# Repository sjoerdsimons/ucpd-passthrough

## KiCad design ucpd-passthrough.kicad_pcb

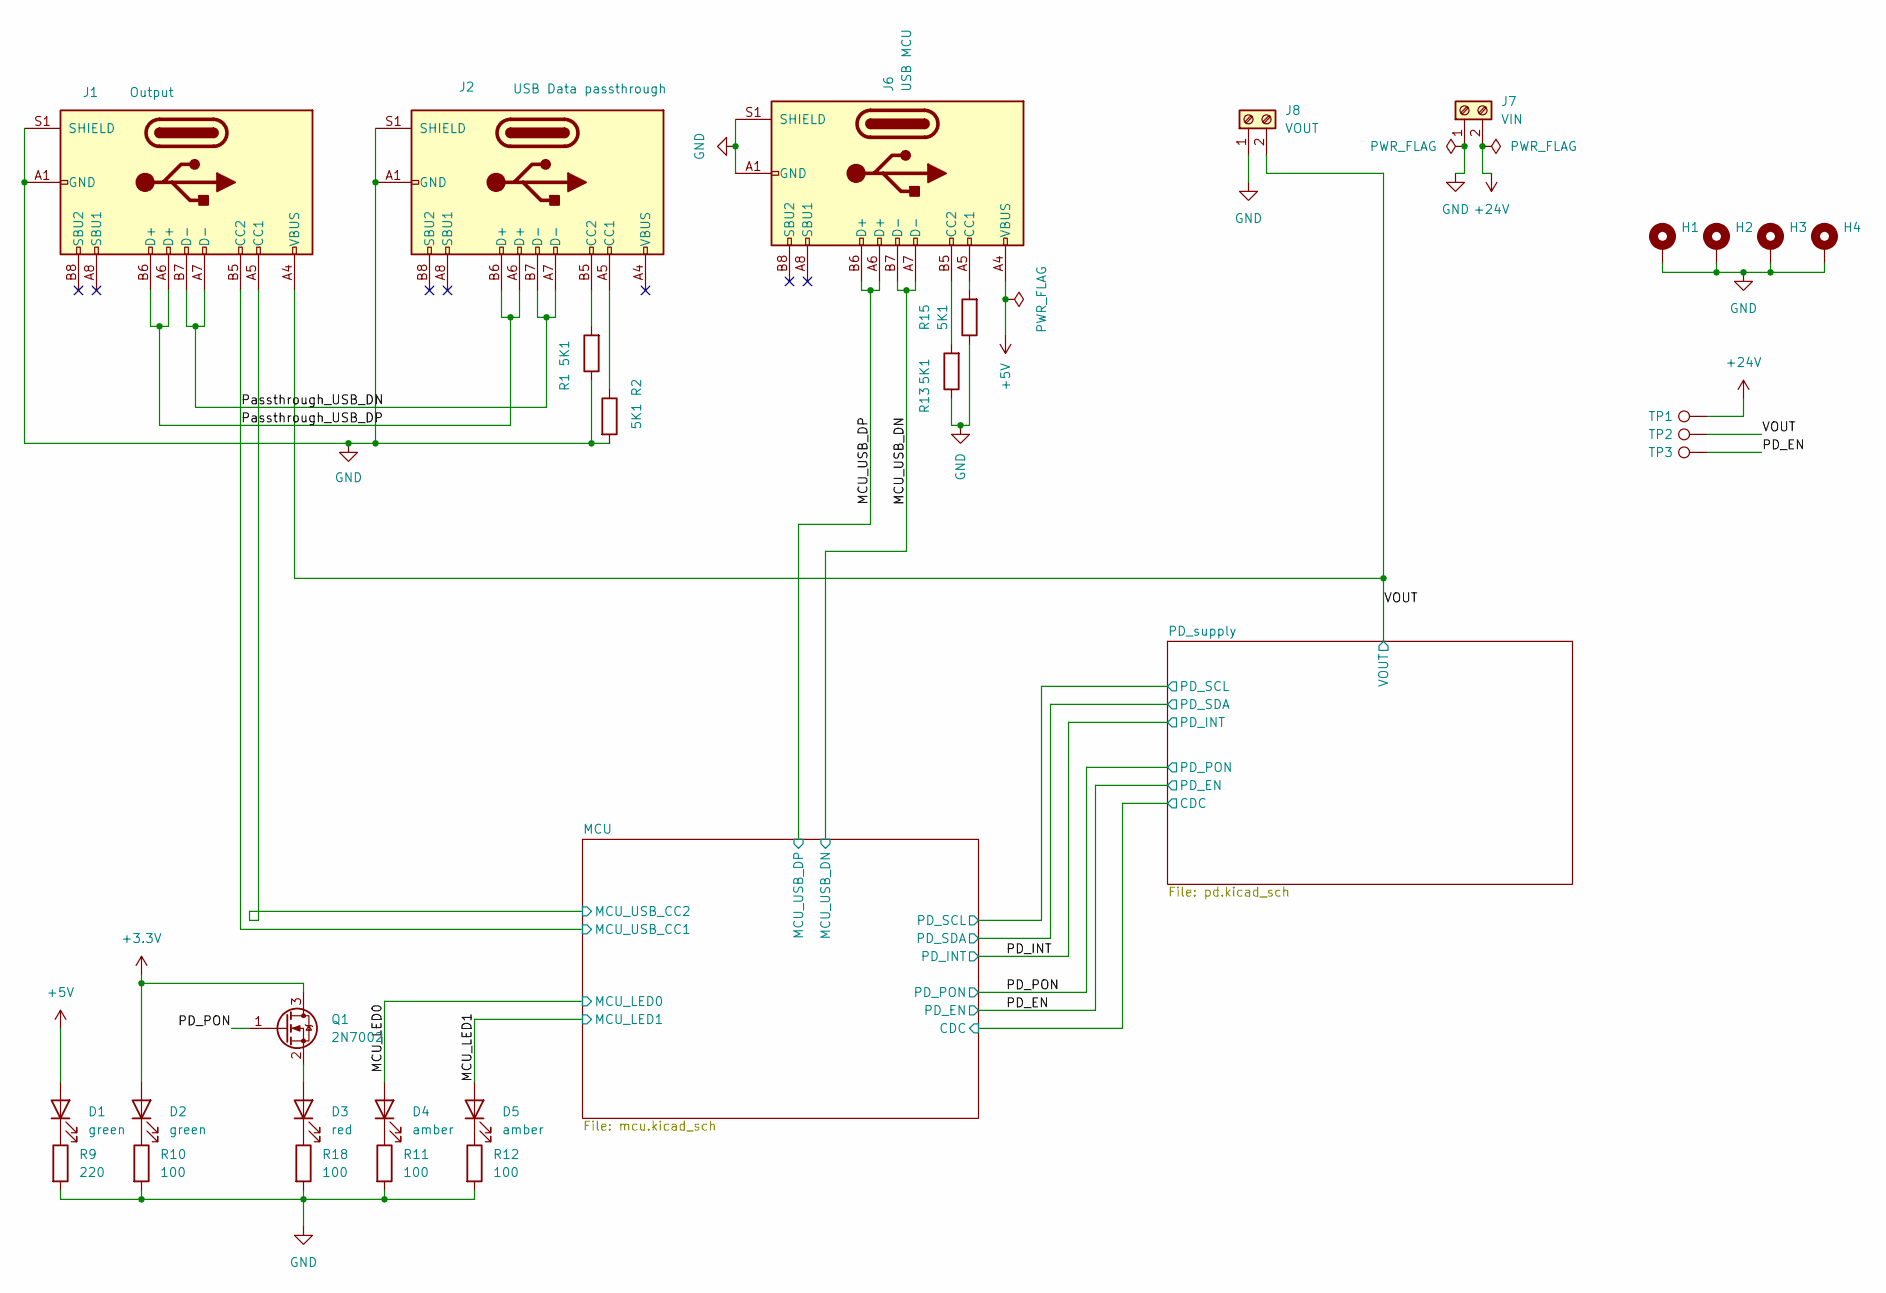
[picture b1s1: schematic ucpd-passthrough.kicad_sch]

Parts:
D1, D2: green; LED_0603_1608Metric; DigiKey 732-4980-1-ND
D3: red; LED_0603_1608Metric; DigiKey 732-4978-1-ND
D4, D5: amber; LED_0603_1608Metric; DigiKey 732-150060AS75000CT-ND
H1, H2, H3, H4: MountingHole_Pad; MountingHole_2.2mm_M2_DIN965_Pad
J1: Output; USB_C_Receptacle_GCT_USB4105-xx-A_16P_TopMnt_Horizontal; DigiKey 2073-USB4105-GF-ACT-ND
J2: USB Data passthrough; USB_C_Receptacle_GCT_USB4105-xx-A_16P_TopMnt_Horizontal; DigiKey 2073-USB4105-GF-ACT-ND
J6: USB MCU; USB_C_Receptacle_GCT_USB4105-xx-A_16P_TopMnt_Horizontal; DigiKey 2073-USB4105-GF-ACT-ND
J7: VIN; TerminalBlock_MaiXu_MX126-5.0-02P_1x02_P5.00mm; DigiKey 732-10955-ND
J8: VOUT; TerminalBlock_MaiXu_MX126-5.0-02P_1x02_P5.00mm; DigiKey 732-10955-ND
Q1: 2N7002; SOT-23; DigiKey 5399-2N7002CT-ND
R1, R2, R13, R15: 5K1; R_0603_1608Metric; DigiKey 13-RC0603FR-105K1LCT-ND
R9: 220; R_0603_1608Metric; DigiKey 311-220HRCT-ND
R10, R11, R12, R18: 100; R_0603_1608Metric; DigiKey 311-100HRCT-ND
TP1, TP2: TestPoint; TestPoint_Pad_D2.0mm
TP3: TestPoint; TestPoint_Pad_D1.0mm

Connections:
+3.3V: D2.2 (A), Q1.3 (D); also elsewhere on the board
+5V: D1.2 (A), J6.A4 (VBUS), J6.A9 (VBUS), J6.B4 (VBUS), J6.B9 (VBUS); also elsewhere on the board
+24V: J7.2, TP1.1; also elsewhere on the board
/MCU/MCU_USB_CC2: J1.A5 (CC1); also elsewhere on the board
/MCU_LED0: D4.2 (A); also elsewhere on the board
/MCU_LED1: D5.2 (A); also elsewhere on the board
/MCU_USB_DN: J6.A7 (D-), J6.B7 (D-); also elsewhere on the board
/MCU_USB_DP: J6.A6 (D+), J6.B6 (D+); also elsewhere on the board
/PD_EN: TP3.1; also elsewhere on the board
/PD_PON: Q1.1 (G); also elsewhere on the board
/VOUT: J1.A4 (VBUS), J1.A9 (VBUS), J1.B4 (VBUS), J1.B9 (VBUS), J8.2, TP2.1; also elsewhere on the board
GND: H1.1, H2.1, H3.1, H4.1, J1.A1 (GND), J1.A12 (GND), J1.B1 (GND), J1.B12 (GND), J1.S1 (SHIELD), J2.A1 (GND), J2.A12 (GND), J2.B1 (GND), J2.B12 (GND), J2.S1 (SHIELD), J6.A1 (GND), J6.A12 (GND), J6.B1 (GND), J6.B12 (GND), J6.S1 (SHIELD), J7.1, J8.1, R1.1, R2.2, R9.2, R10.2, R11.2, R12.2, R13.1, R15.1, R18.2; also elsewhere on the board
unnamed: D1.1 (K), R9.1
unnamed: D2.1 (K), R10.1
unnamed: D3.2 (A), Q1.2 (S)
unnamed: D3.1 (K), R18.1
unnamed: D4.1 (K), R11.1
unnamed: D5.1 (K), R12.1
unnamed: J2.A5 (CC1), R2.1
unnamed: J2.B5 (CC2), R1.2
unnamed: J6.A5 (CC1), R15.2
unnamed: J6.B5 (CC2), R13.2

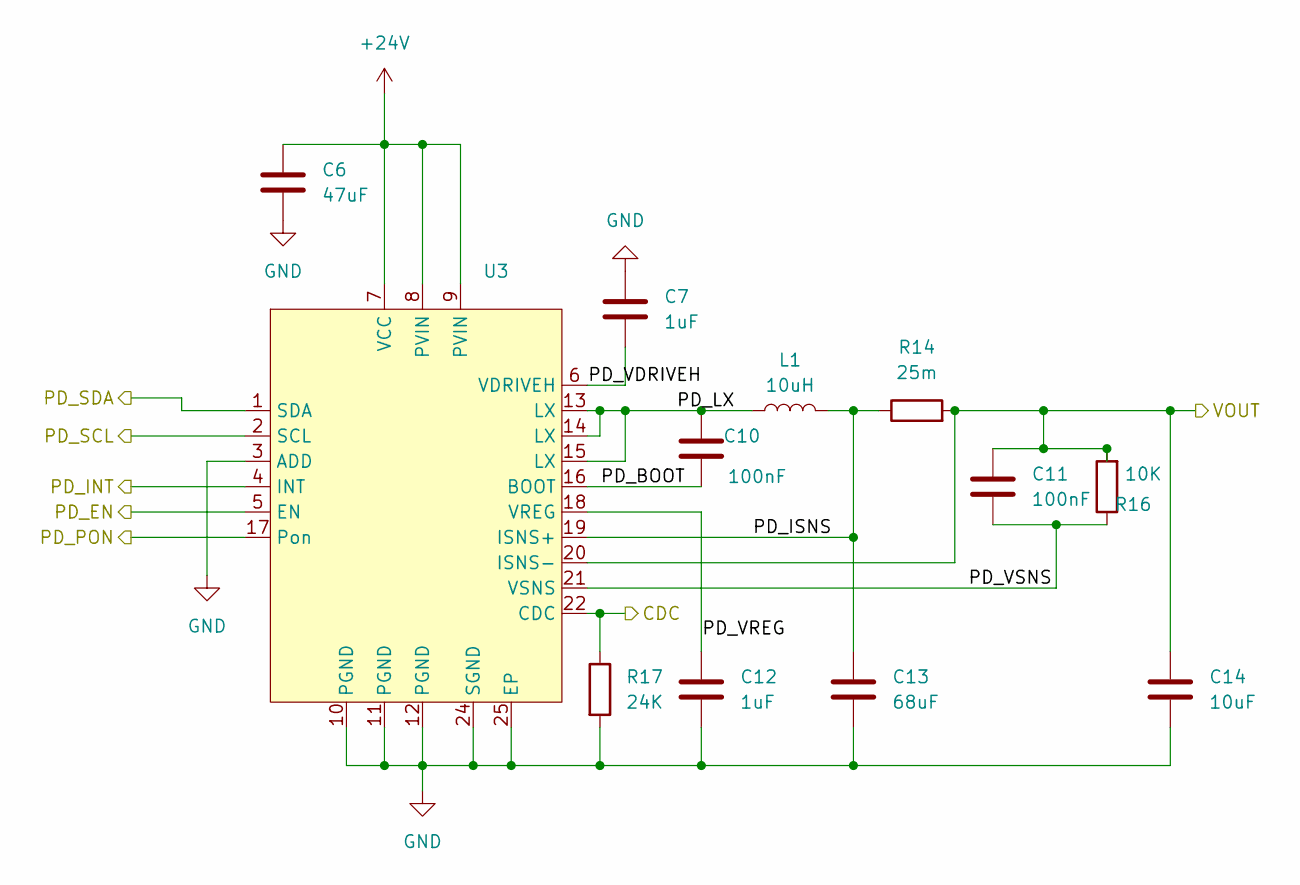
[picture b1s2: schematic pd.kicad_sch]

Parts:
C6: 47uF; CAPC6153X670N; DigiKey 490-16295-1-ND
C7, C12: 1uF; C_0603_1608Metric; DigiKey 1276-1861-1-ND
C10, C11: 100nF; C_0603_1608Metric; DigiKey 1276-1935-1-ND
C13: 68uF; CAP_KRM55_MUR; DigiKey 490-16293-1-ND
C14: 10uF; C_0603_1608Metric; DigiKey 490-GRM188R6YA106MA73JCT-ND
L1: 10uH; IND_SPRH1210-100M; DigiKey 4044-SPRH1210-100MCT-ND
R14: 25m; R_2512_6332Metric_Pad1.40x3.35mm_HandSolder; DigiKey YAG2169CT-ND
R16: 10K; R_0603_1608Metric; DigiKey 311-10.0KHRCT-ND
R17: 24K; R_0603_1608Metric; DigiKey 311-24.0KHRCT-ND
U3: QFN_D01PUR_STM; DigiKey 497-STPD01PURCT-ND

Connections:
+24V: C6.1, U3.7 (VCC), U3.8 (PVIN), U3.9 (PVIN); also elsewhere on the board
/MCU/CDC: R17.1, U3.22 (CDC); also elsewhere on the board
/MCU/PD_SCL: U3.2 (SCL); also elsewhere on the board
/MCU/PD_SDA: U3.1 (SDA); also elsewhere on the board
/PD_EN: U3.5 (EN); also elsewhere on the board
/PD_INT: U3.4 (INT); also elsewhere on the board
/PD_PON: U3.17 (Pon); also elsewhere on the board
/PD_supply/PD_BOOT: C10.1, U3.16 (BOOT)
/PD_supply/PD_ISNS: C13.1, L1.2, R14.1, U3.19 (ISNS+)
/PD_supply/PD_LX: C10.2, L1.1, U3.13 (LX), U3.14 (LX), U3.15 (LX)
/PD_supply/PD_VDRIVEH: C7.2, U3.6 (VDRIVEH)
/PD_supply/PD_VREG: C12.1, U3.18 (VREG)
/PD_supply/PD_VSNS: C11.1, R16.1, U3.21 (VSNS)
/VOUT: C11.2, C14.1, R14.2, R16.2, U3.20 (ISNS-); also elsewhere on the board
GND: C6.2, C7.1, C12.2, C13.2, C14.2, R17.2, U3.3 (ADD), U3.10 (PGND), U3.11 (PGND), U3.12 (PGND), U3.24 (SGND), U3.25 (EP); also elsewhere on the board

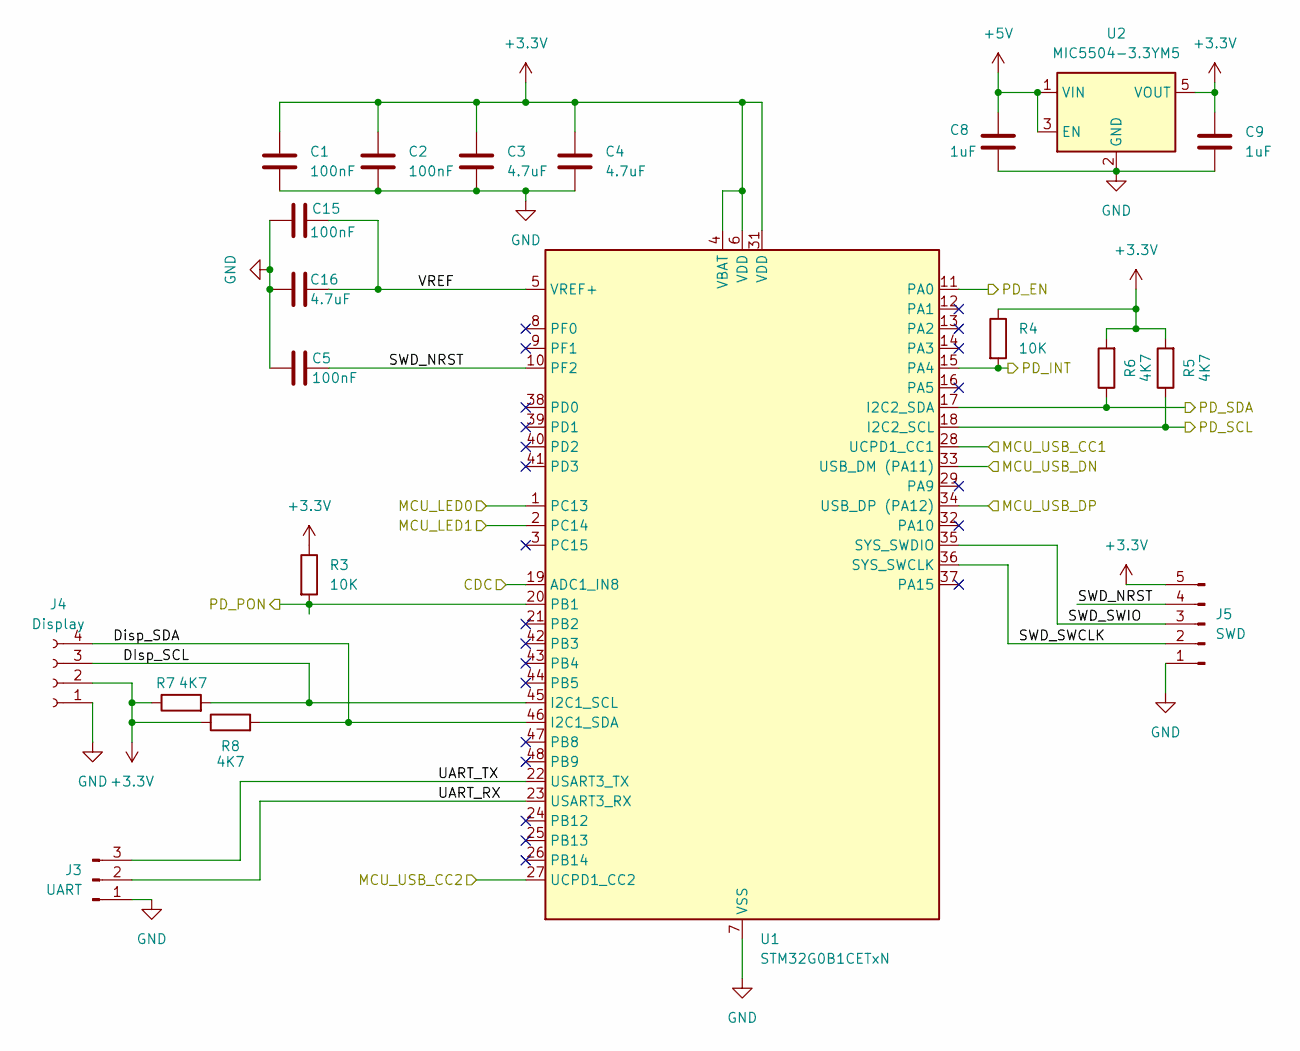
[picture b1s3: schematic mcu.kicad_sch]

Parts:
C1, C2, C5, C15: 100nF; C_0603_1608Metric; DigiKey 1276-1935-1-ND
C3, C4, C16: 4.7uF; C_0603_1608Metric; DigiKey 1276-1045-1-ND
C8, C9: 1uF; C_0603_1608Metric; DigiKey 1276-1861-1-ND
J3: UART; PinHeader_1x03_P2.54mm_Vertical
J4: Display; PinSocket_1x04_P2.54mm_Vertical
J5: SWD; PinHeader_1x05_P2.54mm_Vertical
R3, R4: 10K; R_0603_1608Metric; DigiKey 311-10.0KHRCT-ND
R5, R6, R7, R8: 4K7; R_0603_1608Metric; DigiKey 311-4.70KHRCT-ND
U1: STM32G0B1CETxN; LQFP-48_7x7mm_P0.5mm; DigiKey 497-STM32G0B1CET6N-ND
U2: MIC5504-3.3YM5; SOT-23-5; DigiKey 576-4764-1-ND

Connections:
+3.3V: C1.1, C2.1, C3.1, C4.1, C9.1, J4.2, J5.5, R3.1, R4.1, R5.2, R6.2, R7.1, R8.1, U1.4 (VBAT), U1.6 (VDD), U1.31 (VDD), U2.5 (VOUT); also elsewhere on the board
+5V: C8.1, U2.1 (VIN), U2.3 (EN); also elsewhere on the board
/MCU/CDC: U1.19 (ADC1_IN8); also elsewhere on the board
/MCU/DIsp_SCL: J4.3, R7.2, U1.45 (I2C1_SCL)
/MCU/Disp_SDA: J4.4, R8.2, U1.46 (I2C1_SDA)
/MCU/MCU_USB_CC2: U1.27 (UCPD1_CC2); also elsewhere on the board
/MCU/PD_SCL: R5.1, U1.18 (I2C2_SCL); also elsewhere on the board
/MCU/PD_SDA: R6.1, U1.17 (I2C2_SDA); also elsewhere on the board
/MCU/SWD_NRST: C5.1, J5.4, U1.10 (PF2)
/MCU/SWD_SWCLK: J5.2, U1.36 (SYS_SWCLK)
/MCU/SWD_SWIO: J5.3, U1.35 (SYS_SWDIO)
/MCU/UART_RX: J3.2, U1.23 (USART3_RX)
/MCU/UART_TX: J3.3, U1.22 (USART3_TX)
/MCU/VREF: C15.1, C16.1, U1.5 (VREF+)
/MCU_LED0: U1.1 (PC13); also elsewhere on the board
/MCU_LED1: U1.2 (PC14); also elsewhere on the board
/MCU_USB_DN: U1.33 (USB_DM (PA11)); also elsewhere on the board
/MCU_USB_DP: U1.34 (USB_DP (PA12)); also elsewhere on the board
/PD_EN: U1.11 (PA0); also elsewhere on the board
/PD_INT: R4.2, U1.15 (PA4); also elsewhere on the board
/PD_PON: R3.2, U1.20 (PB1); also elsewhere on the board
GND: C1.2, C2.2, C3.2, C4.2, C5.2, C8.2, C9.2, C15.2, C16.2, J3.1, J4.1, J5.1, U1.7 (VSS), U1.30 (VSS), U2.2 (GND); also elsewhere on the board

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
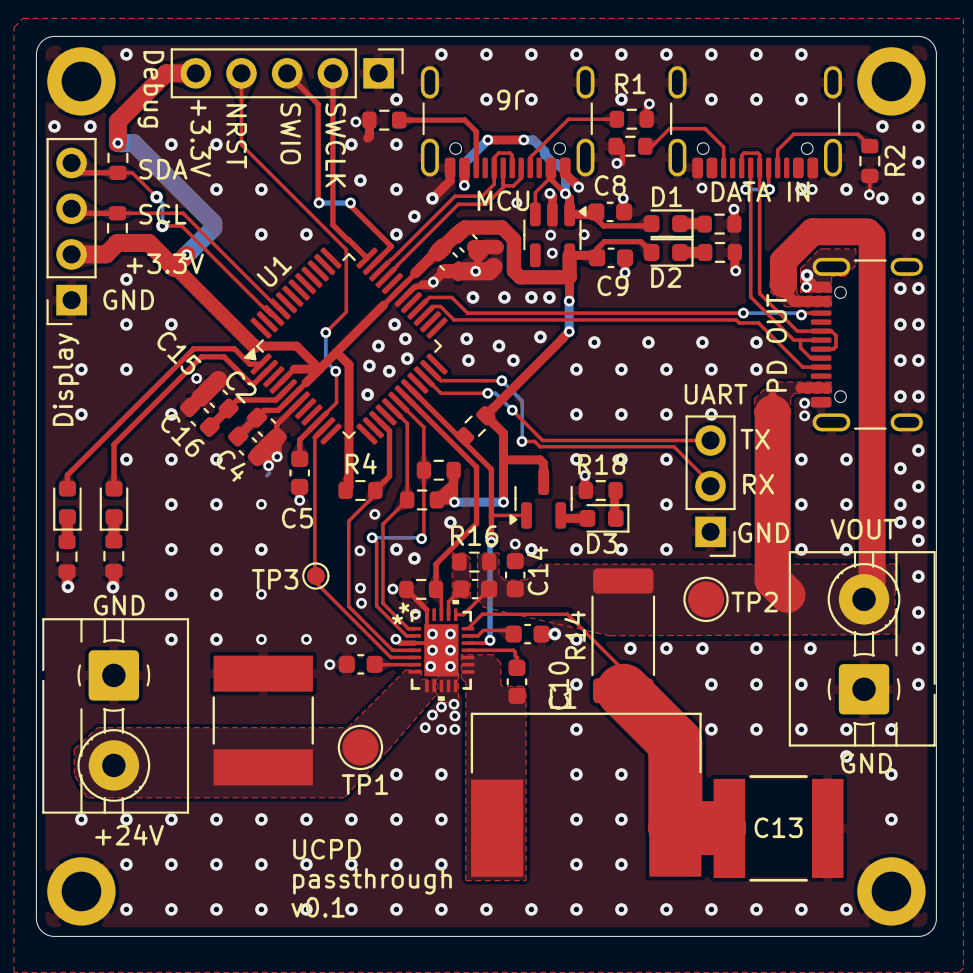
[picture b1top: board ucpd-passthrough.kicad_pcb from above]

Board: 2 copper layers, 50.0 x 50.0 mm, 59 parts (0 on the bottom side), 43 nets.

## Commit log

2025-02-09 ucpd-passthrough v0.1 design
2025-02-17 clean up fabrication layer
2025-02-21 Update pcb values from schematic
2025-02-22 firmware: minimal hi
2025-02-22 Enable display
2025-02-28 Clarify licenses
